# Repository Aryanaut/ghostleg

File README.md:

# ghostleg
Repository for the development of an acoustically and bio-mechanically accurate leg phantom.

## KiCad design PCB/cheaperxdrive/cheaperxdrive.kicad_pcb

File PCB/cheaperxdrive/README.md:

# ghostleg
Repository for the development of an acoustically and bio-mechanically accurate leg phantom.

reference schematics:
https://github.com/odriverobotics/ODriveHardware/blob/master/v3/v3.5docs/schematic_v3.5.pdf
https://github.com/makerbase-mks/ODrive-MKS/blob/main/Hardware/MKS%20ODrive_S%20schematic_v3.6.pdf
https://github.com/antonchromjak/MINI4/blob/master/MINI4.pdf

design requirements:
- single sided PCB to be fabricated with JLCPCB, try to keep cost within 35SGD per unit. single sided standard may be cheaper than economic.
- motor peak current is unlikely to exceed 30A, use mosfet JMSL0302AG. package and pinout of mosfets in schematic are compatible.
- all other components to be kept the same
- CANbus for communication

notes:
- Skipping the thermistors and temperature senseing section.

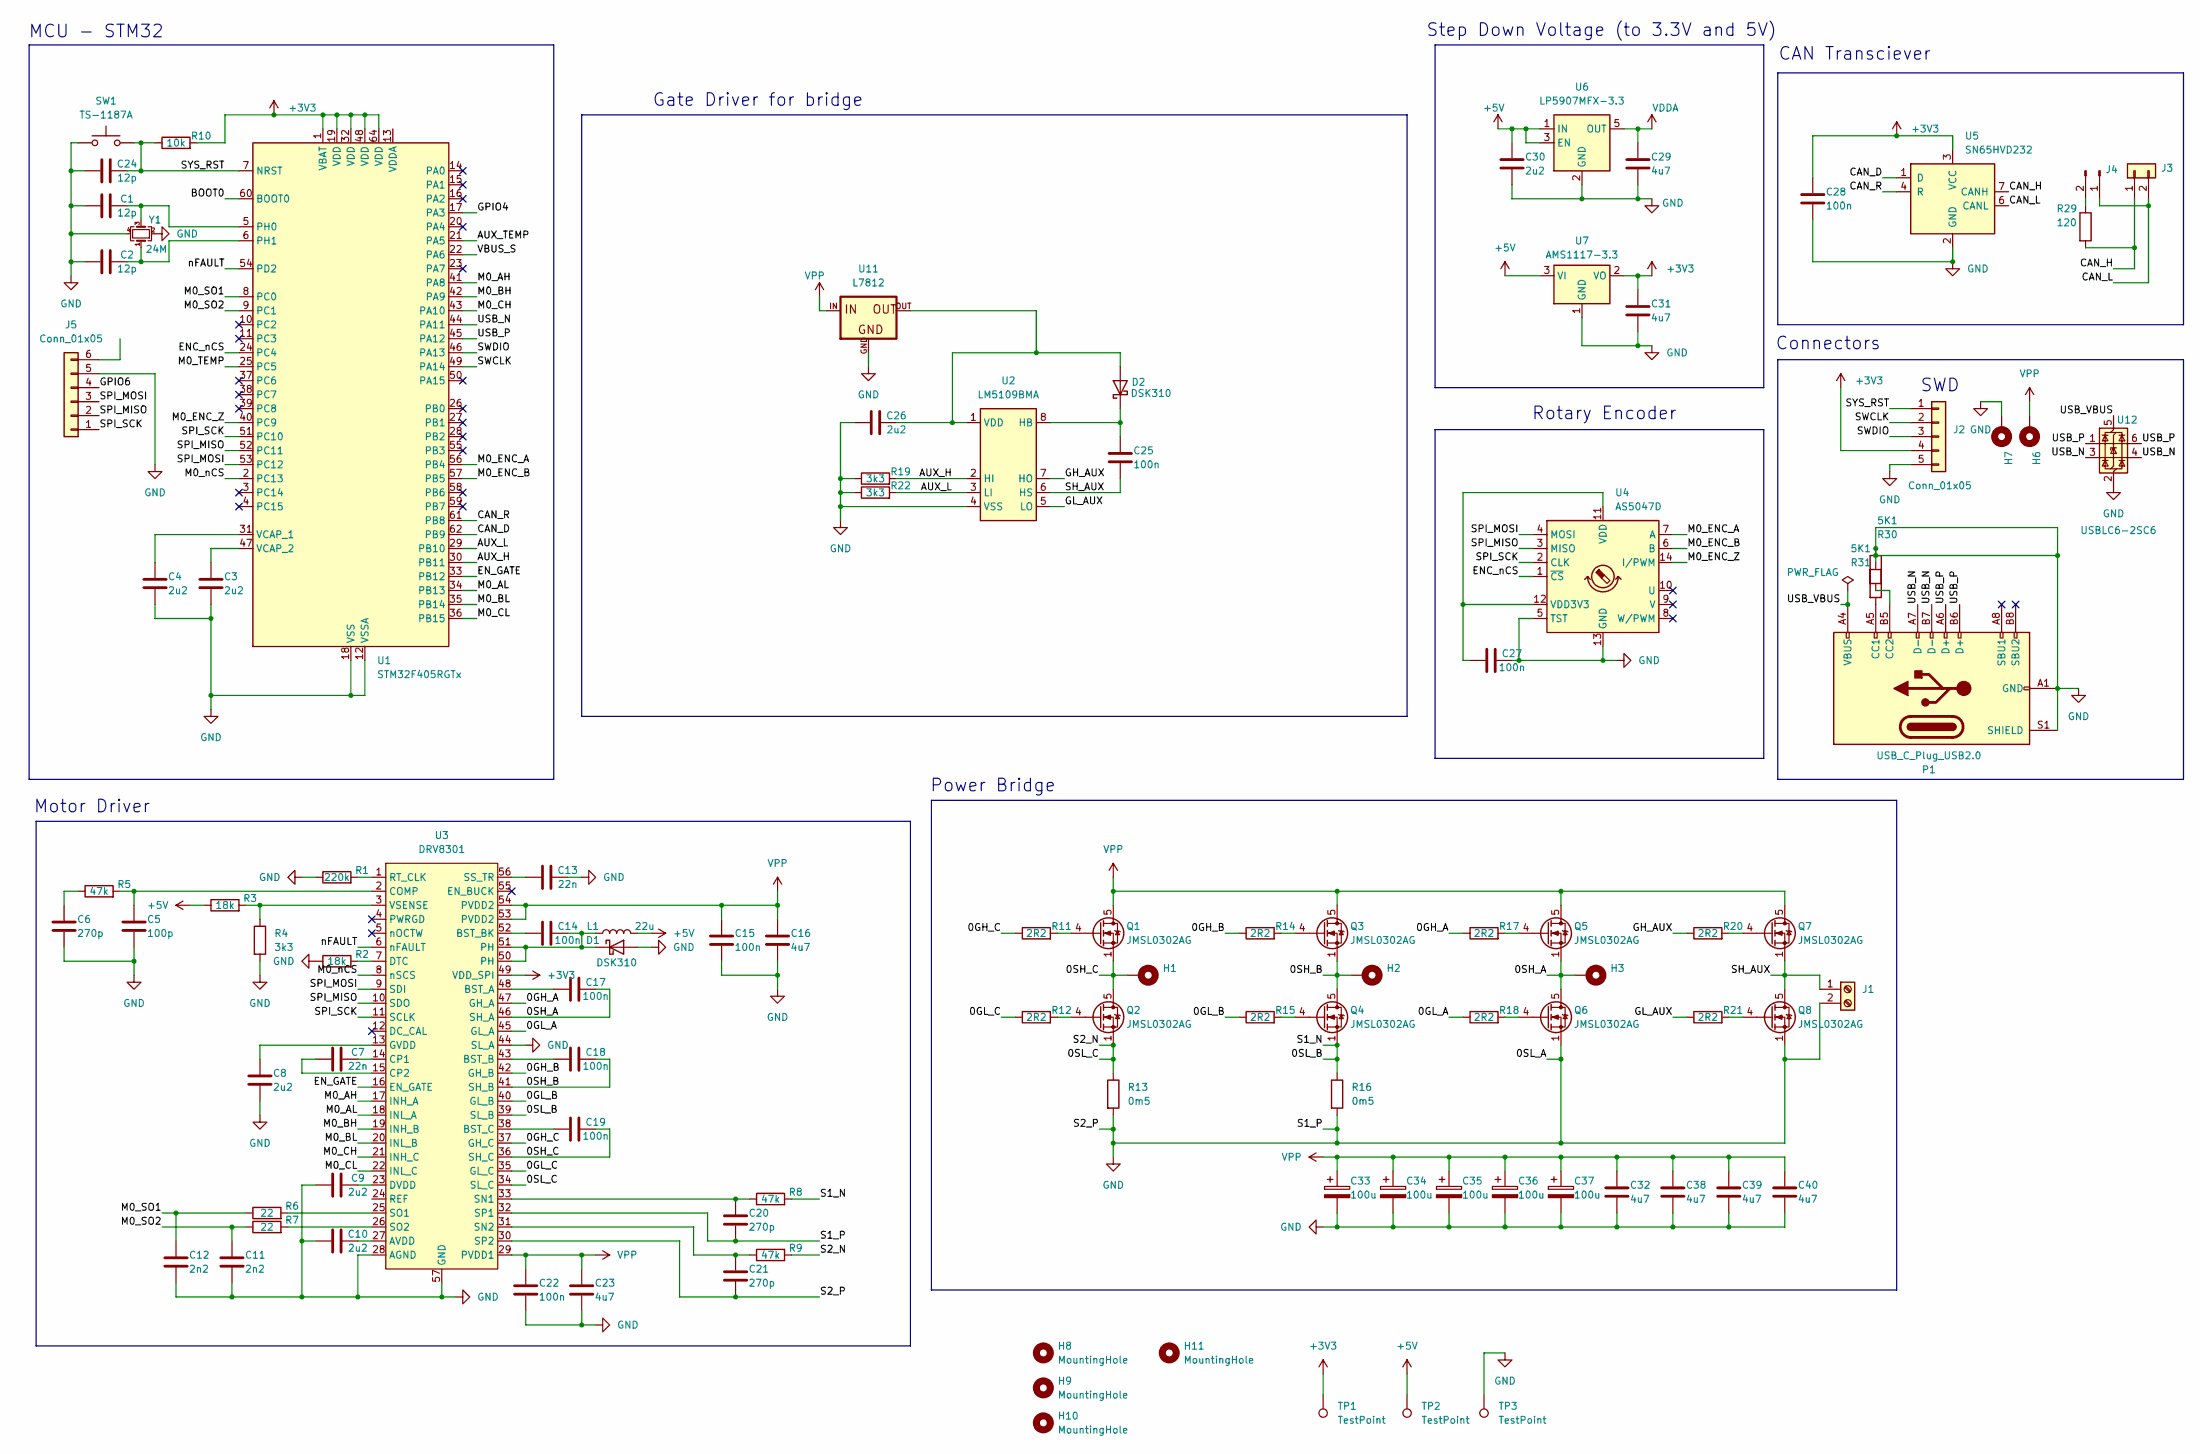
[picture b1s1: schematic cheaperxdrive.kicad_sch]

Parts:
C1, C2, C24: 12p; C_0201_0603Metric
C3, C4, C8, C9, C10, C26, C30: 2u2; C_0201_0603Metric
C5: 100p; C_0201_0603Metric
C6, C20, C21: 270p; C_0201_0603Metric
C7, C13: 22n; C_0201_0603Metric
C11, C12: 2n2; C_0201_0603Metric
C14, C15, C17, C18, C19, C22, C25, C27, C28: 100n; C_0201_0603Metric
C16, C23, C29, C31, C32, C38, C39, C40: 4u7; C_0201_0603Metric
C33, C34, C35, C36, C37: 100u; CP_Radial_D5.0mm_P2.50mm
D1, D2: DSK310; C_0201_0603Metric
H1, H2, H3, H6, H7: MountingHole_Pad; MountingHole_4.3mm_M4_Pad_Via
H8, H9, H10, H11: MountingHole; MountingHole_3.2mm_M3
J1: Screw_Terminal_01x02; TerminalBlock_Phoenix_MPT-0,5-2-2.54_1x02_P2.54mm_Horizontal
J2: Conn_01x05; JST_EH_B5B-EH-A_1x05_P2.50mm_Vertical
J3: Conn_01x02; JST_XH_B2B-XH-AM_1x02_P2.50mm_Vertical
J4: Conn_01x02_Pin; PinHeader_1x02_P2.54mm_Vertical
J5: Conn_01x05; JST_EH_B6B-EH-A_1x06_P2.50mm_Vertical
L1: 22u; L_0201_0603Metric
P1: USB_C_Plug_USB2.0; USB_C_Receptacle_HRO_TYPE-C-31-M-12
Q1, Q2, Q3, Q4, Q5, Q6, Q7, Q8: JMSL0302AG; TDSON-8-1
R1: 220k; R_0201_0603Metric
R2, R3: 18k; R_0201_0603Metric
R4, R19, R22: 3k3; R_0201_0603Metric
R5, R8, R9: 47k; R_0201_0603Metric
R6, R7: 22; R_0201_0603Metric
R10: 10k; R_0201_0603Metric
R11, R12, R14, R15, R17, R18, R20, R21: 2R2; R_0201_0603Metric
R13, R16: 0m5; R_0201_0603Metric
R29: 120; R_0201_0603Metric
R30, R31: 5K1; R_0201_0603Metric
SW1: TS-1187A; SW_SPST_CK_RS282G05A3
TP1, TP2, TP3: TestPoint; TestPoint_Pad_D2.5mm
U1: STM32F405RGTx; LQFP-64_10x10mm_P0.5mm
U2: LM5109BMA; SOIC-8_3.9x4.9mm_P1.27mm
U3: DRV8301; HTSSOP-56-1EP_6.1x14mm_P0.5mm_EP3.61x6.35mm
U4: AS5047D; TSSOP-14_4.4x5mm_P0.65mm
U5: SN65HVD232; SOIC-8_3.9x4.9mm_P1.27mm
U6: LP5907MFX-3.3; SOT-23-5
U7: AMS1117-3.3; SOT-223-3_TabPin2
U11: L7812; 78XXS
U12: USBLC6-2SC6; SOT-23-6
Y1: 24M; Crystal_SMD_3225-4Pin_3.2x2.5mm

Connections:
+3V3: C28.1, C31.1, J2.4, R10.2, TP1.1, U1.1 (VBAT), U1.19 (VDD), U1.32 (VDD), U1.48 (VDD), U1.64 (VDD), U3.49 (VDD_SPI), U5.3 (VCC), U7.2 (VO)
+5V: C30.1, L1.2, R3.1, TP2.1, U6.1 (IN), U6.3 (EN), U7.3 (VI)
/0GH_A: R17.1, U3.47 (GH_A)
/0GH_B: R14.1, U3.42 (GH_B)
/0GH_C: R11.1, U3.37 (GH_C)
/0GL_A: R18.1, U3.45 (GL_A)
/0GL_B: R15.1, U3.40 (GL_B)
/0GL_C: R12.1, U3.35 (GL_C)
/0SH_A: C17.2, H3.1, Q5.1 (S), Q5.2 (S), Q5.3 (S), Q6.5 (D), U3.46 (SH_A)
/0SH_B: C18.2, H2.1, Q3.1 (S), Q3.2 (S), Q3.3 (S), Q4.5 (D), U3.41 (SH_B)
/0SH_C: C19.2, H1.1, Q1.1 (S), Q1.2 (S), Q1.3 (S), Q2.5 (D), U3.36 (SH_C)
/0SL_B: Q4.1 (S), Q4.2 (S), Q4.3 (S), R8.2, R16.1, U3.39 (SL_B)
/0SL_C: Q2.1 (S), Q2.2 (S), Q2.3 (S), R9.2, R13.1, U3.34 (SL_C)
/AUX_H: R19.2, U1.30 (PB11), U2.2 (HI)
/AUX_L: R22.2, U1.29 (PB10), U2.3 (LI)
/AUX_TEMP: U1.21 (PA5)
/BOOT0: U1.60 (BOOT0)
/CAN_D: U1.62 (PB9), U5.1 (D)
/CAN_H: J3.1, R29.2, U5.7 (CANH)
/CAN_L: J3.2, J4.1, U5.6 (CANL)
/CAN_R: U1.61 (PB8), U5.4 (R)
/ENC_nCS: U1.24 (PC4), U4.1 (~CS)
/EN_GATE: U1.33 (PB12), U3.16 (EN_GATE)
/GH_AUX: R20.1, U2.7 (HO)
/GL_AUX: R21.1, U2.5 (LO)
/GPIO4: U1.17 (PA3)
/GPIO6: J5.4
/M0_AH: U1.41 (PA8), U3.17 (INH_A)
/M0_AL: U1.34 (PB13), U3.18 (INL_A)
/M0_BH: U1.42 (PA9), U3.19 (INH_B)
/M0_BL: U1.35 (PB14), U3.20 (INL_B)
/M0_CH: U1.43 (PA10), U3.21 (INH_C)
/M0_CL: U1.36 (PB15), U3.22 (INL_C)
/M0_ENC_A: U1.56 (PB4), U4.7 (A)
/M0_ENC_B: U1.57 (PB5), U4.6 (B)
/M0_ENC_Z: U1.40 (PC9), U4.14 (I/PWM)
/M0_SO1: C12.1, R6.1, U1.8 (PC0)
/M0_SO2: C11.1, R7.1, U1.9 (PC1)
/M0_TEMP: U1.25 (PC5)
/M0_nCS: U1.2 (PC13), U3.8 (nSCS)
/SH_AUX: C25.2, J1.1, Q7.1 (S), Q7.2 (S), Q7.3 (S), Q8.5 (D), U2.6 (HS)
/SPI_MISO: J5.2, U1.52 (PC11), U3.10 (SDO), U4.3 (MISO)
/SPI_MOSI: J5.3, U1.53 (PC12), U3.9 (SDI), U4.4 (MOSI)
/SPI_SCK: J5.1, U1.51 (PC10), U3.11 (SCLK), U4.2 (CLK)
/SWCLK: J2.2, U1.49 (PA14)
/SWDIO: J2.3, U1.46 (PA13)
/SYS_RST: C24.2, J2.1, R10.1, SW1.2, U1.7 (NRST)
/USB_N: P1.A7 (D-), P1.B7 (D-), U1.44 (PA11), U12.3 (I/O2), U12.4 (I/O2)
/USB_P: P1.A6 (D+), P1.B6 (D+), U1.45 (PA12), U12.1 (I/O1), U12.6 (I/O1)
/USB_VBUS: P1.A4 (VBUS), P1.A9 (VBUS), P1.B4 (VBUS), P1.B9 (VBUS), U12.5 (VBUS)
/VBUS_S: U1.22 (PA6)
/nFAULT: U1.54 (PD2), U3.6 (nFAULT)
GND: C1.1, C2.1, C3.2, C4.2, C5.2, C6.2, C8.2, C9.1, C10.1, C11.2, C12.2, C13.2, C15.2, C16.2, C20.2, C21.2, C22.2, C23.2, C24.1, C26.1, C27.2, C28.2, C29.2, C30.2, C31.2, C32.2, C33.2, C34.2, C35.2, C36.2, C37.2, C38.2, C39.2, C40.2, D1.2 (A), H7.1, J1.2, J2.5, J5.5, P1.A1 (GND), P1.A12 (GND), P1.B1 (GND), P1.B12 (GND), P1.S1 (SHIELD), Q6.1 (S), Q6.2 (S), Q6.3 (S), Q8.1 (S), Q8.2 (S), Q8.3 (S), R1.1, R2.1, R4.2, R13.2, R16.2, R19.1, R22.1, R30.1, R31.1, SW1.1, TP3.1, U1.12 (VSSA), U1.18 (VSS), U1.63 (VSS), U2.4 (VSS), U3.28 (AGND), U3.30 (SP2), U3.32 (SP1), U3.44 (SL_A), U3.57 (GND), U4.5 (TST), U4.13 (GND), U5.2 (GND), U6.2 (GND), U7.1 (GND), U11.GND, U12.2 (GND), Y1.2, Y1.4
unnamed: C6.1, R5.1
unnamed: C14.2, D1.1 (K), L1.1, U3.50 (PH), U3.51 (PH)
unnamed: C26.2, D2.2 (A), U2.1 (VDD), U11.OUT
unnamed: C25.1, D2.1 (K), U2.8 (HB)
unnamed: J4.2, R29.1
unnamed: P1.A5 (CC1), R31.2
unnamed: P1.B5 (CC2), R30.2
unnamed: Q1.4 (G), R11.2
unnamed: Q2.4 (G), R12.2
unnamed: Q3.4 (G), R14.2
unnamed: Q4.4 (G), R15.2
unnamed: Q5.4 (G), R17.2
unnamed: Q6.4 (G), R18.2
unnamed: Q7.4 (G), R20.2
unnamed: Q8.4 (G), R21.2
unnamed: C1.2, U1.5 (PH0), Y1.3
unnamed: C2.2, U1.6 (PH1), Y1.1
unnamed: C4.1, U1.31 (VCAP_1)
unnamed: C3.1, U1.47 (VCAP_2)
unnamed: C10.2, U3.27 (AVDD)
unnamed: C17.1, U3.48 (BST_A)
unnamed: C18.1, U3.43 (BST_B)
unnamed: C14.1, U3.52 (BST_BK)
unnamed: C19.1, U3.38 (BST_C)
unnamed: C5.1, R5.2, U3.2 (COMP)
unnamed: C7.2, U3.14 (CP1)
unnamed: C7.1, U3.15 (CP2)
unnamed: R2.2, U3.7 (DTC)
unnamed: C9.2, U3.23 (DVDD)
unnamed: C8.1, U3.13 (GVDD)
unnamed: R1.2, U3.1 (RT_CLK)
unnamed: C20.1, R8.1, U3.33 (SN1)
unnamed: C21.1, R9.1, U3.31 (SN2)
unnamed: R6.2, U3.25 (SO1)
unnamed: R7.2, U3.26 (SO2)
unnamed: C13.1, U3.56 (SS_TR)
unnamed: R3.2, R4.1, U3.3 (VSENSE)
unnamed: C27.1, U4.11 (VDD), U4.12 (VDD3V3)
VDDA: C29.1, U6.5 (OUT)
VPP: C15.1, C16.1, C22.1, C23.1, C32.1, C33.1, C34.1, C35.1, C36.1, C37.1, C38.1, C39.1, C40.1, H6.1, Q1.5 (D), Q3.5 (D), Q5.5 (D), Q7.5 (D), U3.29 (PVDD1), U3.53 (PVDD2), U3.54 (PVDD2), U11.IN

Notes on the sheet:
Power Bridge
Step Down Voltage (to 3.3V and 5V)
Motor Driver
SWD
Rotary Encoder
MCU - STM32
CAN Transciever
Connectors
Gate Driver for bridge

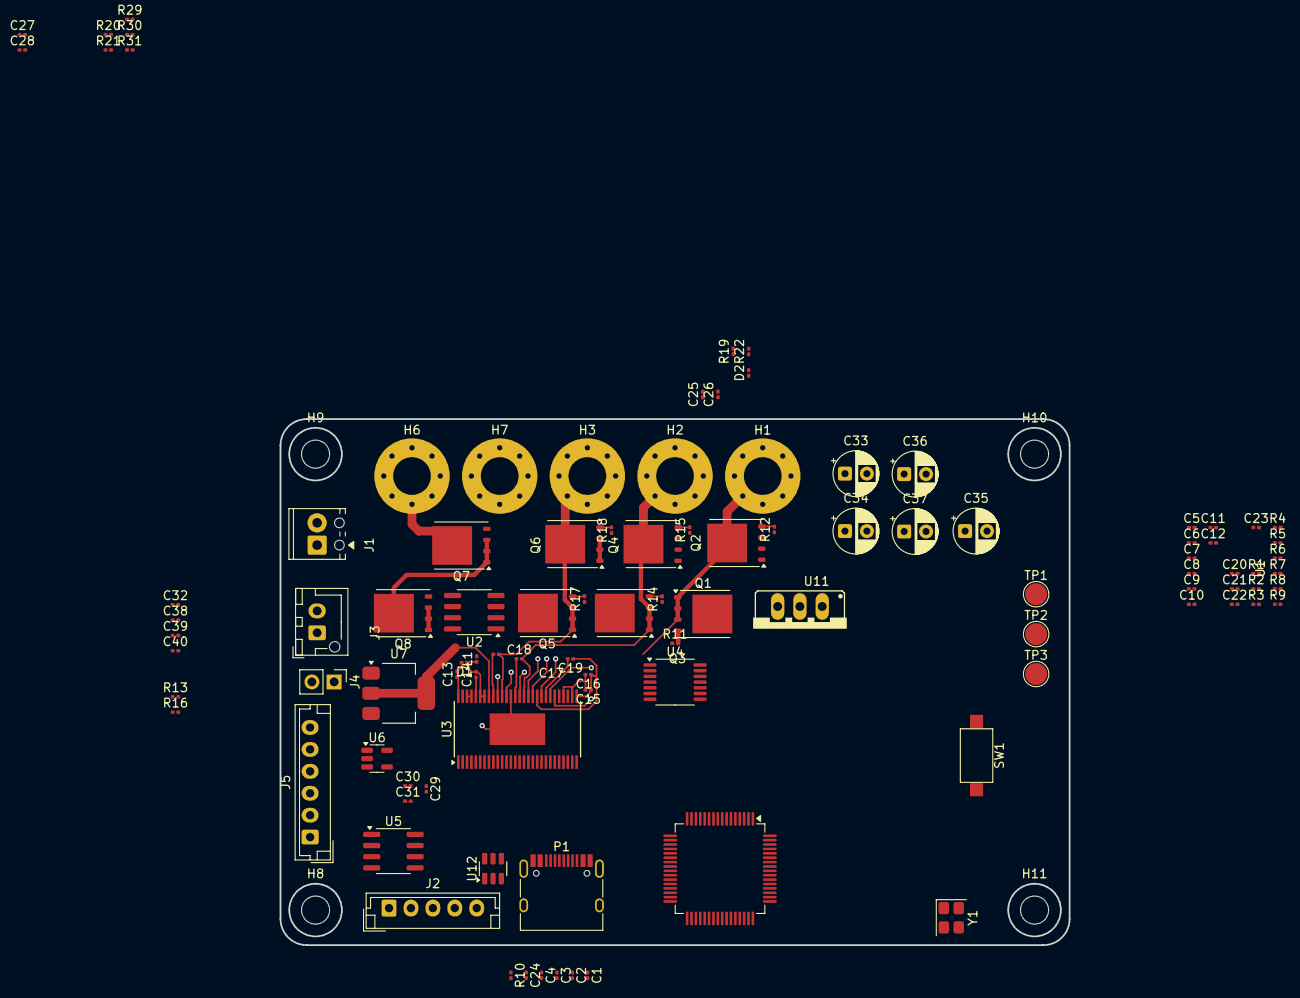
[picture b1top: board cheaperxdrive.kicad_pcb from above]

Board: 2 copper layers, 90.0 x 60.0 mm, 105 parts (0 on the bottom side), 87 nets.
